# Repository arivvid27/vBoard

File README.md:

# vBoard

## Overview
This project is a custom-built mechanical keyboard created to replace a failing, non-ergonomic office keyboard used by my English teacher, which was causing him noticeable hand strain during long grading sessions. 

The goal was to build a reliable, tactile, and comfortable typing tool tailored for high-volume daily classroom use.

## Why I Built It
* **Solving a Real Problem:** Standard membrane office keyboards lack tactile feedback, force heavy bottom-outs, and offer no ergonomic support. Watching a favorite teacher struggle with physical discomfort on a broken board made this a high-impact problem to solve.
* **Hands-on Curiosity:** I had always wanted to build a custom mechanical keyboard from scratch to learn about hardware assembly, switch physics, and custom keymapping.

## Features & Specs
* **Ergonomic Layout:** Compact footprint designed to reduce unnecessary reach and wrist movement.
* **Tactile Switches:** Selected for clear physical feedback without requiring excessive actuation force, helping reduce finger fatigue.
* **Custom Keycaps:** Clean, comfortable profile designed for long typing sessions.

## What I Learned
* **Hardware Assembly:** Learned component compatibility across PCBs, plates, switches, and stabilizers, along with basic soldering and hardware assembly.
* **Ergonomics & Physical Health:** Explored how keycap profiles, switch actuation points, and board angles directly affect wrist strain and overall typing comfort.
* **Firmware Configuration:** Discovered how to program custom keymaps and function layers to streamline everyday typing and shortcut tasks.

## Pinout:

## Finished Schematic in KiCad

## Finished PCB in KiCad

## PCB in CAD:

## Finished CAD Models:

## Pricing:
### PCB Fabrication:

### Amazon Cart with Parts:

(PS, I need an Orpheus Pico with this, I just don't know how I'm supposed to get one without KEEB)

## IRL Build (Will post later)

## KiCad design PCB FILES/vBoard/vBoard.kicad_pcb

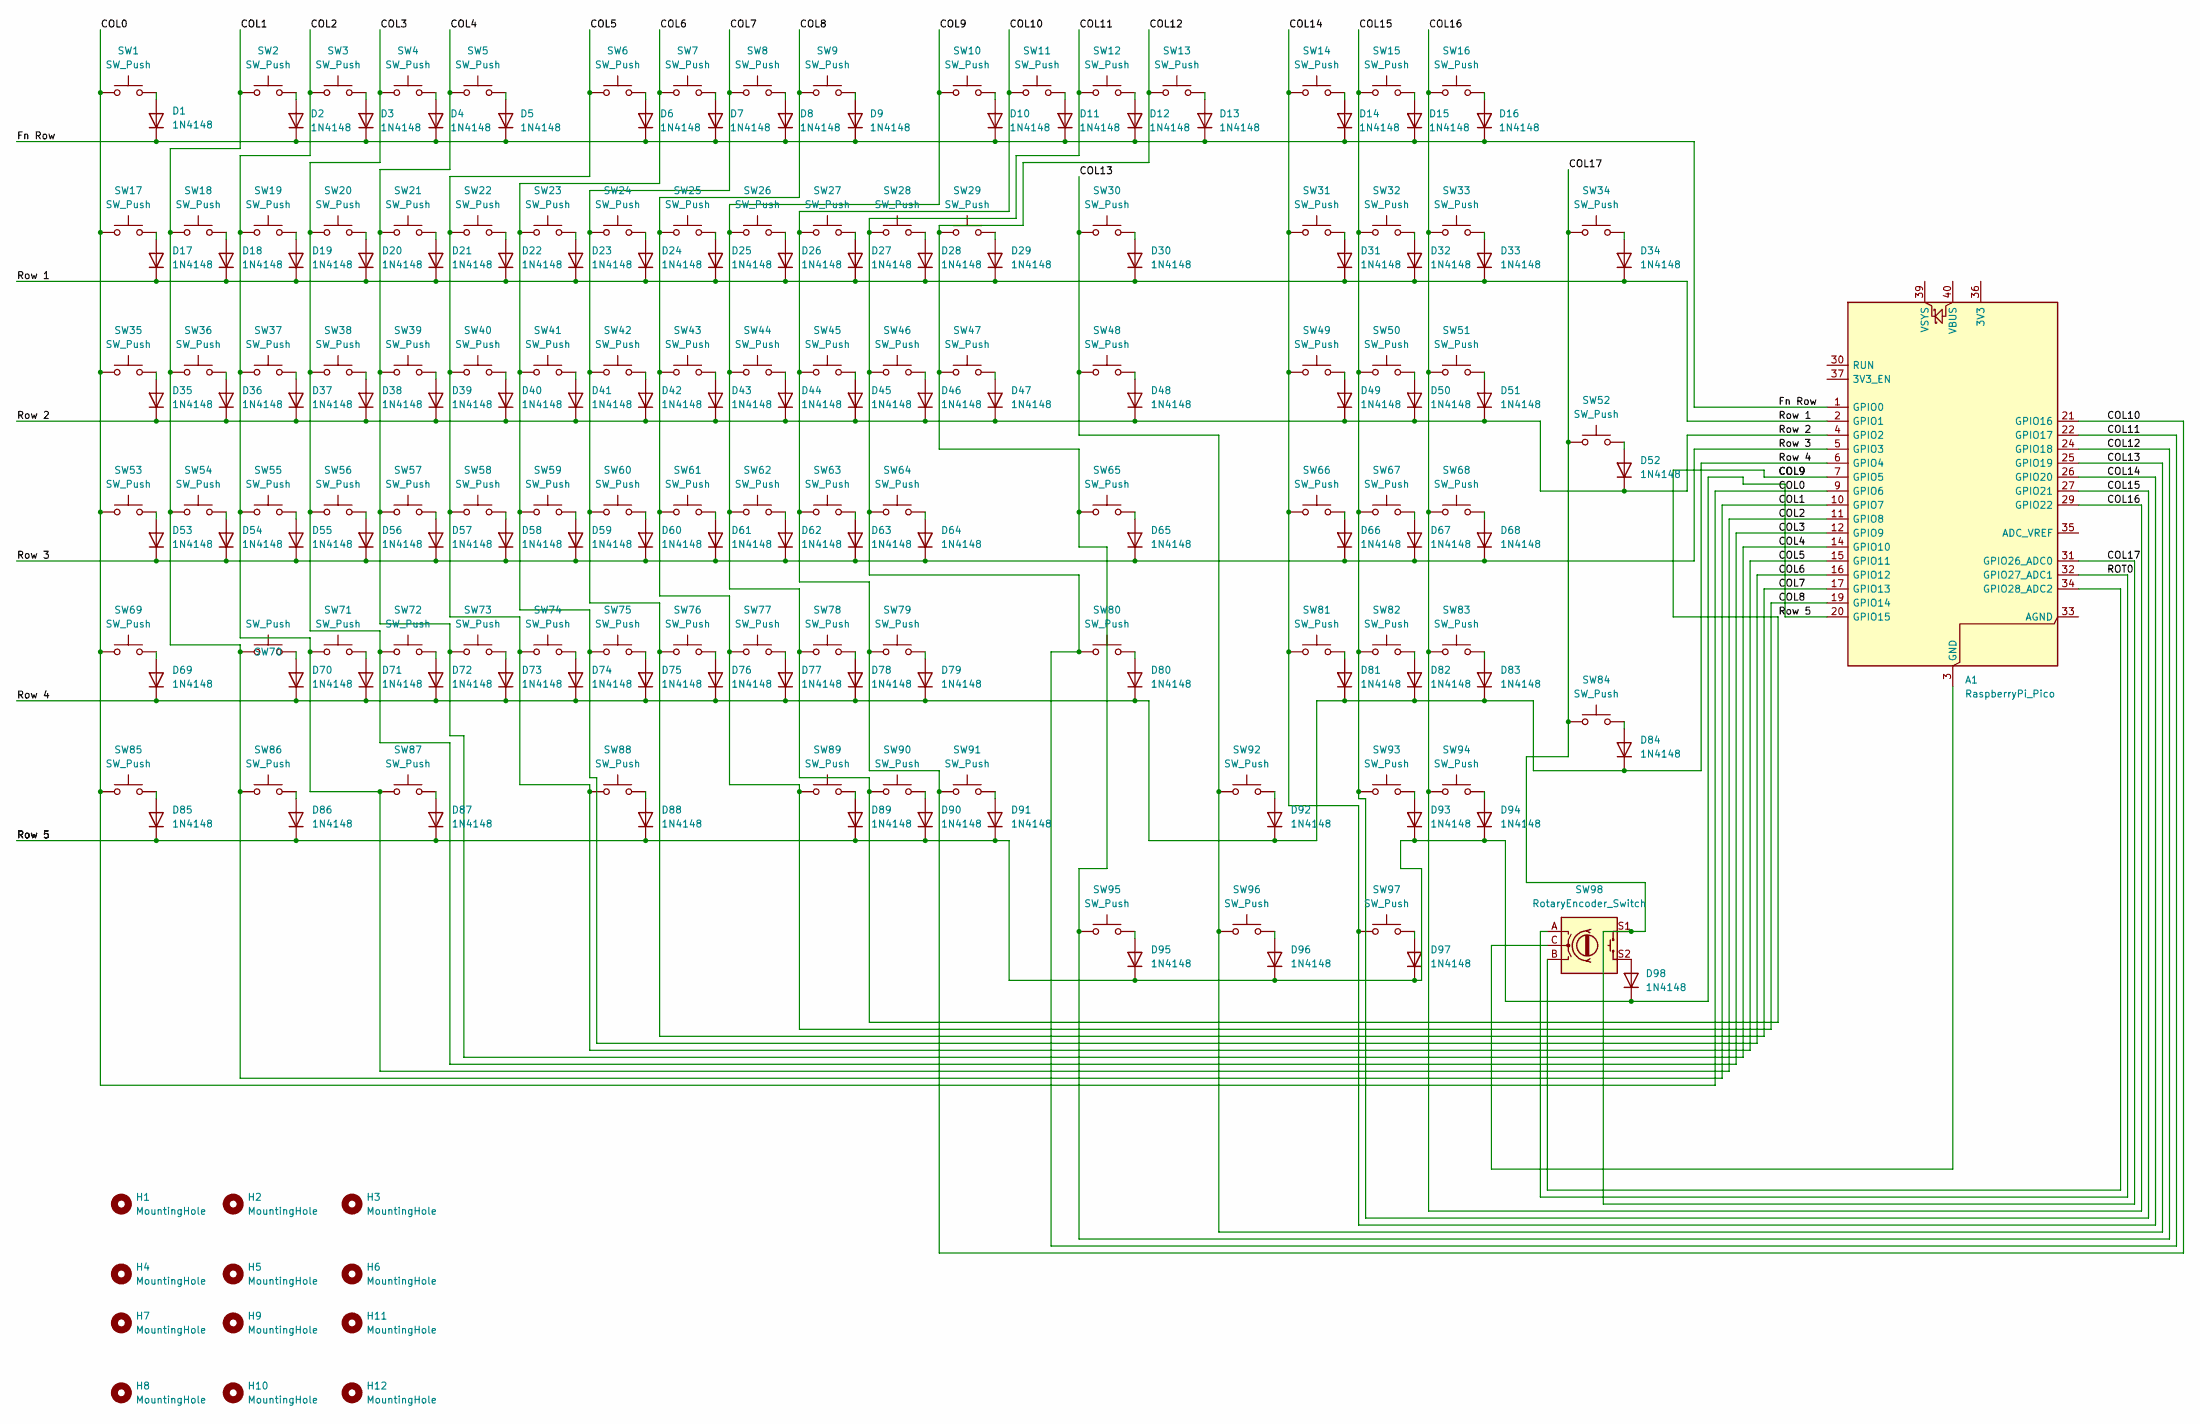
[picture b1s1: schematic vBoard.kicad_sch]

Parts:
A1: RaspberryPi_Pico; RaspberryPi_Pico_Common_THT
D1, D2, D3, D4, D5, D6, D7, D8, D9, D10, D11, D12, D13, D14, D15, D16, D17, D18, D19, D20, D21, D22, D23, D24, D25, D26, D27, D28, D29, D30, D31, D32, D33, D34, D35, D36, D37, D38, D39, D40, D41, D42, D43, D44, D45, D46, D47, D48, D49, D50, D51, D52, D53, D54, D55, D56, D57, D58, D59, D60, D61, D62, D63, D64, D65, D66, D67, D68, D69, D70, D71, D72, D73, D74, D75, D76, D77, D78, D79, D80, D81, D82, D83, D84, D85, D86, D87, D88, D89, D90, D91, D92, D93, D94, D95, D96, D97, D98: 1N4148; D_SOD-123
H1, H2, H3, H4, H5, H6, H7, H8, H9, H10, H11, H12: MountingHole; MountingHole_3.2mm_M3
SW1, SW2, SW3, SW4, SW5, SW6, SW7, SW8, SW9, SW10, SW11, SW12, SW13, SW14, SW15, SW16, SW17, SW18, SW19, SW20, SW21, SW22, SW23, SW24, SW25, SW26, SW27, SW28, SW29, SW30, SW31, SW32, SW33, SW34, SW35, SW36, SW37, SW38, SW39, SW40, SW41, SW42, SW43, SW44, SW45, SW46, SW47, SW48, SW49, SW50, SW51, SW52, SW53, SW54, SW55, SW56, SW57, SW58, SW59, SW60, SW61, SW62, SW63, SW64, SW65, SW66, SW67, SW68, SW69, SW70, SW71, SW72, SW73, SW74, SW75, SW76, SW77, SW78, SW79, SW80, SW81, SW82, SW83, SW84, SW85, SW86, SW87, SW88, SW89, SW90, SW91, SW92, SW93, SW94, SW95, SW96, SW97: SW_Push; SW_MX_HS_CPG151101S11_1u
SW98: RotaryEncoder_Switch; RotaryEncoder_Alps_EC11E-Switch_Vertical_H20mm

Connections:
/COL0: A1.9 (GPIO6), SW1.1, SW17.1, SW35.1, SW53.1, SW69.1, SW85.1
/COL1: A1.10 (GPIO7), SW2.1, SW18.1, SW36.1, SW54.1, SW70.1, SW86.1
/COL2: A1.11 (GPIO8), SW3.1, SW19.1, SW37.1, SW55.1, SW71.1, SW87.1
/COL3: A1.12 (GPIO9), SW4.1, SW20.1, SW38.1, SW56.1, SW72.1
/COL4: A1.14 (GPIO10), SW5.1, SW21.1, SW39.1, SW57.1, SW73.1
/COL5: A1.15 (GPIO11), SW6.1, SW22.1, SW40.1, SW58.1, SW74.1, SW88.1
/COL6: A1.16 (GPIO12), SW7.1, SW23.1, SW41.1, SW59.1, SW75.1
/COL7: A1.17 (GPIO13), SW8.1, SW24.1, SW42.1, SW60.1, SW76.1
/COL8: A1.19 (GPIO14), SW9.1, SW25.1, SW43.1, SW61.1, SW77.1, SW89.1
/COL9: A1.7 (GPIO5), A1.20 (GPIO15), D85.1 (K), D86.1 (K), D87.1 (K), D88.1 (K), D89.1 (K), D90.1 (K), D91.1 (K), D93.1 (K), D94.1 (K), D95.1 (K), D96.1 (K), D97.1 (K), D98.1 (K), SW10.1, SW26.1, SW44.1, SW62.1, SW78.1, SW90.1
/COL10: A1.21 (GPIO16), SW11.1, SW27.1, SW45.1, SW63.1, SW79.1, SW91.1
/COL11: A1.22 (GPIO17), SW12.1, SW28.1, SW46.1, SW64.1, SW80.1
/COL12: A1.24 (GPIO18), SW13.1, SW29.1, SW47.1, SW65.1, SW95.1
/COL13: A1.25 (GPIO19), SW30.1, SW48.1, SW92.1, SW96.1
/COL14: A1.26 (GPIO20), SW14.1, SW31.1, SW49.1, SW66.1, SW81.1, SW97.1
/COL15: A1.27 (GPIO21), SW15.1, SW32.1, SW50.1, SW67.1, SW82.1, SW93.1
/COL16: A1.29 (GPIO22), SW16.1, SW33.1, SW51.1, SW68.1, SW83.1, SW94.1
/COL17: A1.31 (GPIO26_ADC0), SW34.1, SW52.1, SW84.1, SW98.S1
/Fn Row: A1.1 (GPIO0), D1.1 (K), D2.1 (K), D3.1 (K), D4.1 (K), D5.1 (K), D6.1 (K), D7.1 (K), D8.1 (K), D9.1 (K), D10.1 (K), D11.1 (K), D12.1 (K), D13.1 (K), D14.1 (K), D15.1 (K), D16.1 (K)
/ROT0: A1.32 (GPIO27_ADC1), SW98.A
/Row 1: A1.2 (GPIO1), D17.1 (K), D18.1 (K), D19.1 (K), D20.1 (K), D21.1 (K), D22.1 (K), D23.1 (K), D24.1 (K), D25.1 (K), D26.1 (K), D27.1 (K), D28.1 (K), D29.1 (K), D30.1 (K), D31.1 (K), D32.1 (K), D33.1 (K), D34.1 (K)
/Row 2: A1.4 (GPIO2), D35.1 (K), D36.1 (K), D37.1 (K), D38.1 (K), D39.1 (K), D40.1 (K), D41.1 (K), D42.1 (K), D43.1 (K), D44.1 (K), D45.1 (K), D46.1 (K), D47.1 (K), D48.1 (K), D49.1 (K), D50.1 (K), D51.1 (K), D52.1 (K)
/Row 3: A1.5 (GPIO3), D53.1 (K), D54.1 (K), D55.1 (K), D56.1 (K), D57.1 (K), D58.1 (K), D59.1 (K), D60.1 (K), D61.1 (K), D62.1 (K), D63.1 (K), D64.1 (K), D65.1 (K), D66.1 (K), D67.1 (K), D68.1 (K)
/Row 4: A1.6 (GPIO4), D69.1 (K), D70.1 (K), D71.1 (K), D72.1 (K), D73.1 (K), D74.1 (K), D75.1 (K), D76.1 (K), D77.1 (K), D78.1 (K), D79.1 (K), D80.1 (K), D81.1 (K), D82.1 (K), D83.1 (K), D84.1 (K), D92.1 (K)
unnamed: A1.3 (GND), A1.8 (GND), A1.13 (GND), A1.18 (GND), A1.23 (GND), A1.28 (GND), A1.38 (GND), SW98.C
unnamed: A1.34 (GPIO28_ADC2), SW98.B
unnamed: D1.2 (A), SW1.2
unnamed: D2.2 (A), SW2.2
unnamed: D3.2 (A), SW3.2
unnamed: D4.2 (A), SW4.2
unnamed: D5.2 (A), SW5.2
unnamed: D6.2 (A), SW6.2
unnamed: D7.2 (A), SW7.2
unnamed: D8.2 (A), SW8.2
unnamed: D9.2 (A), SW9.2
unnamed: D10.2 (A), SW10.2
unnamed: D11.2 (A), SW11.2
unnamed: D12.2 (A), SW12.2
unnamed: D13.2 (A), SW13.2
unnamed: D14.2 (A), SW14.2
unnamed: D15.2 (A), SW15.2
unnamed: D16.2 (A), SW16.2
unnamed: D17.2 (A), SW17.2
unnamed: D18.2 (A), SW18.2
unnamed: D19.2 (A), SW19.2
unnamed: D20.2 (A), SW20.2
unnamed: D21.2 (A), SW21.2
unnamed: D22.2 (A), SW22.2
unnamed: D23.2 (A), SW23.2
unnamed: D24.2 (A), SW24.2
unnamed: D25.2 (A), SW25.2
unnamed: D26.2 (A), SW26.2
unnamed: D27.2 (A), SW27.2
unnamed: D28.2 (A), SW28.2
unnamed: D29.2 (A), SW29.2
unnamed: D30.2 (A), SW30.2
unnamed: D31.2 (A), SW31.2
unnamed: D32.2 (A), SW32.2
unnamed: D33.2 (A), SW33.2
unnamed: D34.2 (A), SW34.2
unnamed: D35.2 (A), SW35.2
unnamed: D36.2 (A), SW36.2
unnamed: D37.2 (A), SW37.2
unnamed: D38.2 (A), SW38.2
unnamed: D39.2 (A), SW39.2
unnamed: D40.2 (A), SW40.2
unnamed: D41.2 (A), SW41.2
unnamed: D42.2 (A), SW42.2
unnamed: D43.2 (A), SW43.2
unnamed: D44.2 (A), SW44.2
unnamed: D45.2 (A), SW45.2
unnamed: D46.2 (A), SW46.2
unnamed: D47.2 (A), SW47.2
unnamed: D48.2 (A), SW48.2
unnamed: D49.2 (A), SW49.2
unnamed: D50.2 (A), SW50.2
unnamed: D51.2 (A), SW51.2
unnamed: D52.2 (A), SW52.2
unnamed: D53.2 (A), SW53.2
unnamed: D54.2 (A), SW54.2
unnamed: D55.2 (A), SW55.2
unnamed: D56.2 (A), SW56.2
unnamed: D57.2 (A), SW57.2
unnamed: D58.2 (A), SW58.2
unnamed: D59.2 (A), SW59.2
unnamed: D60.2 (A), SW60.2
unnamed: D61.2 (A), SW61.2
unnamed: D62.2 (A), SW62.2
unnamed: D63.2 (A), SW63.2
unnamed: D64.2 (A), SW64.2
unnamed: D65.2 (A), SW65.2
unnamed: D66.2 (A), SW66.2
unnamed: D67.2 (A), SW67.2
unnamed: D68.2 (A), SW68.2
unnamed: D69.2 (A), SW69.2
unnamed: D70.2 (A), SW70.2
unnamed: D71.2 (A), SW71.2
unnamed: D72.2 (A), SW72.2
unnamed: D73.2 (A), SW73.2
unnamed: D74.2 (A), SW74.2
unnamed: D75.2 (A), SW75.2
unnamed: D76.2 (A), SW76.2
unnamed: D77.2 (A), SW77.2
unnamed: D78.2 (A), SW78.2
unnamed: D79.2 (A), SW79.2
unnamed: D80.2 (A), SW80.2
unnamed: D81.2 (A), SW81.2
unnamed: D82.2 (A), SW82.2
unnamed: D83.2 (A), SW83.2
unnamed: D84.2 (A), SW84.2
unnamed: D85.2 (A), SW85.2
unnamed: D86.2 (A), SW86.2
unnamed: D87.2 (A), SW87.2
unnamed: D88.2 (A), SW88.2
unnamed: D89.2 (A), SW89.2
unnamed: D90.2 (A), SW90.2
unnamed: D91.2 (A), SW91.2
unnamed: D92.2 (A), SW92.2
unnamed: D93.2 (A), SW93.2
unnamed: D94.2 (A), SW94.2
unnamed: D95.2 (A), SW95.2
unnamed: D96.2 (A), SW96.2
unnamed: D97.2 (A), SW97.2
unnamed: D98.2 (A), SW98.S2

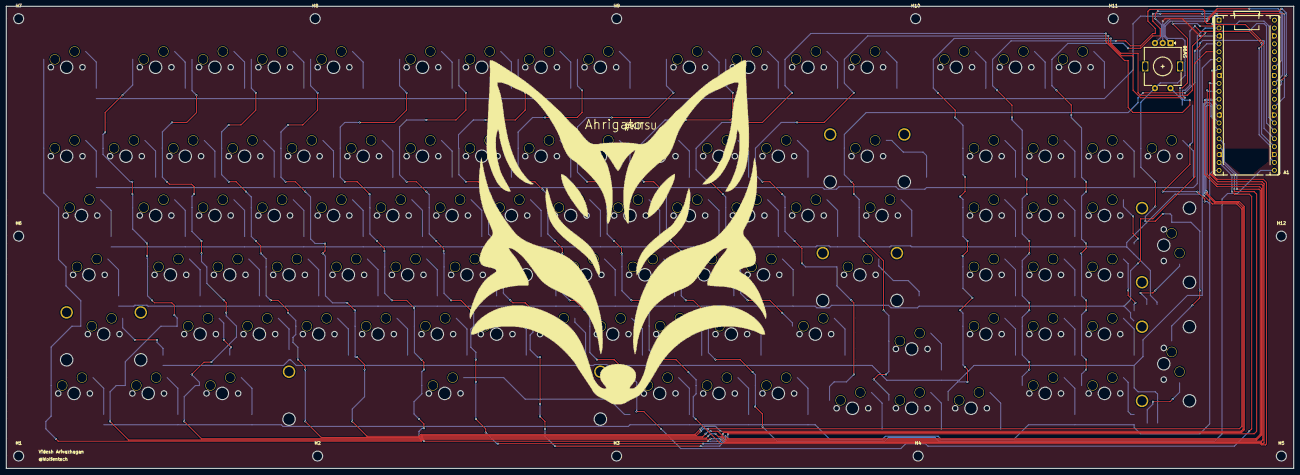
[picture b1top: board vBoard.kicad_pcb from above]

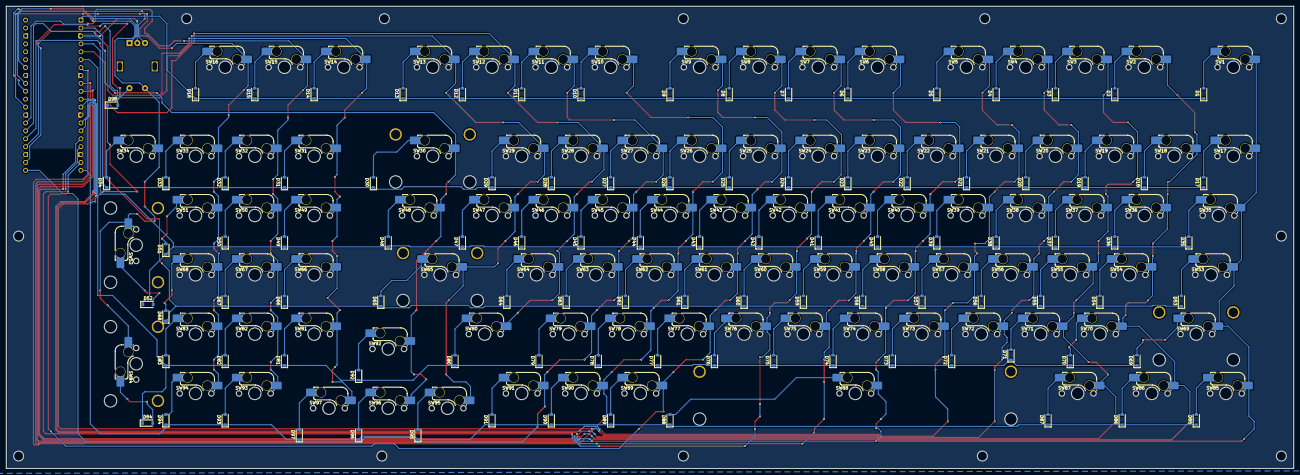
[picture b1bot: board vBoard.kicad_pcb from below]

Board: 2 copper layers, 413.5 x 148.4 mm, 215 parts (197 on the bottom side), 124 nets.

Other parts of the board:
S1, S2, S3, S4, S5: MX_stab; STAB_MX_P_2u
S11: MX_stab; STAB_MX_P_6.25u
